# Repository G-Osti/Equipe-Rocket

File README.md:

Pasta da documentação recuperada de 2022/2023 das atividades desenvolvidas na Equipe Rocket.
Não está nem um pouco organizado.

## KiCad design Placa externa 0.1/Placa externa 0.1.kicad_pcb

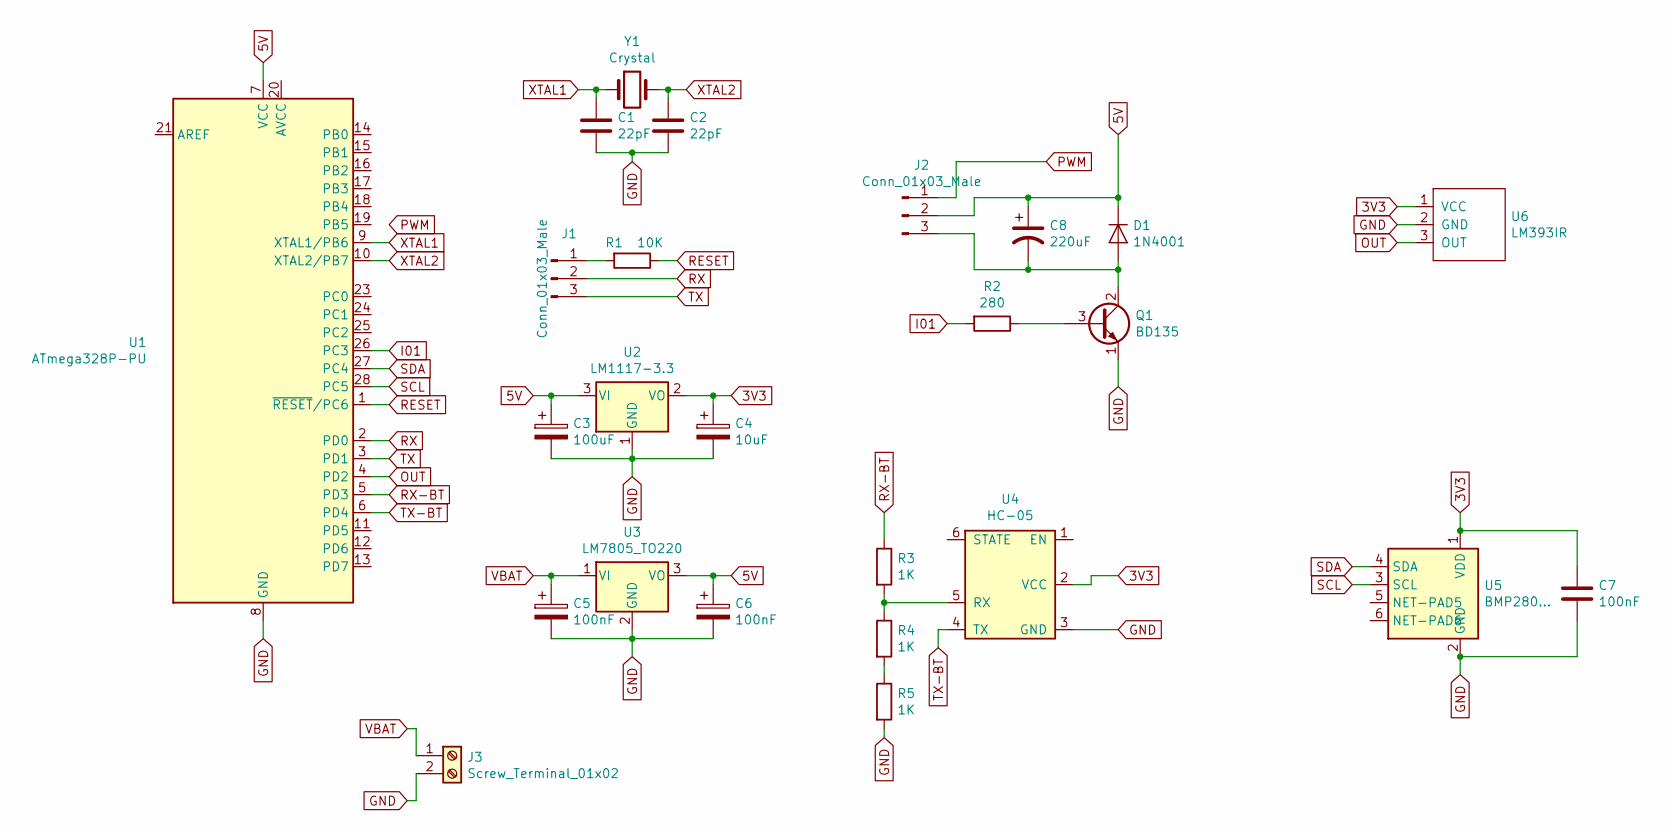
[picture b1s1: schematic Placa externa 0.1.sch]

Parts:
C1, C2: 22pF; CP_EIA-1608-08_AVX-J_Pad1.25x1.05mm_HandSolder
C3: 100uF; CP_EIA-1608-08_AVX-J_Pad1.25x1.05mm_HandSolder
C4: 10uF; CP_EIA-1608-08_AVX-J_Pad1.25x1.05mm_HandSolder
C5, C6, C7: 100nF; CP_EIA-6032-15_Kemet-U_Pad2.25x2.35mm_HandSolder
C8: 220uF; CP_EIA-1608-08_AVX-J_Pad1.25x1.05mm_HandSolder
D1: 1N4001; D_0603_1608Metric_Pad1.05x0.95mm_HandSolder
J1, J2: Conn_01x03_Male; FanPinHeader_1x03_P2.54mm_Vertical
J3: Screw_Terminal_01x02; TerminalBlock_Altech_AK300-2_P5.00mm
Q1: BD135; TO-126-3_Vertical
R1: 10K; R_0603_1608Metric_Pad1.05x0.95mm_HandSolder
R2: 280; R_0603_1608Metric_Pad1.05x0.95mm_HandSolder
R3, R4, R5: 1K; R_0603_1608Metric_Pad1.05x0.95mm_HandSolder
U1: ATmega328P-PU; DIP-28_W7.62mm
U2: LM1117-3.3; TO-3P-3_Vertical
U3: LM7805_TO220; TO-220-3_Vertical
U4: HC-05; SOIC-8_3.9x4.9mm_P1.27mm
U5: BMP280...; Bosch_LGA-8_2x2.5mm_P0.65mm_ClockwisePinNumbering
U6: LM393IR; TO-3P-3_Vertical
Y1: Crystal; Crystal_C26-LF_D2.1mm_L6.5mm_Horizontal

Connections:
3V3: C4.1, C7.1, U2.2 (VO), U4.2 (VCC), U5.1 (VDD), U6.1 (VCC)
5V: C3.1, C6.1, C8.1, D1.1 (K), J2.2, U1.7 (VCC), U2.3 (VI), U3.3 (VO)
GND: C1.2, C2.2, C3.2, C4.2, C5.2, C6.2, C7.2, J3.2, Q1.1 (E), R5.2, U1.8 (GND), U1.22 (GND), U2.1 (GND), U3.2 (GND), U4.3 (GND), U5.2 (GND), U6.2 (GND)
I01: R2.2, U1.26 (PC3)
unnamed: C8.2, D1.2 (A), J2.3, Q1.2 (C)
unnamed: J1.1, R1.2
unnamed: Q1.3 (B), R2.1
unnamed: R3.2, R4.1, U4.5 (RX)
unnamed: R4.2, R5.1
OUT: U1.4 (PD2), U6.3 (OUT)
PWM: J2.1
RESET: R1.1, U1.1 (~RESET~/PC6)
RX: J1.2, U1.2 (PD0)
RX-BT: R3.1, U1.5 (PD3)
SCL: U1.28 (PC5), U5.3 (SCL)
SDA: U1.27 (PC4), U5.4 (SDA)
TX: J1.3, U1.3 (PD1)
TX-BT: U1.6 (PD4), U4.4 (TX)
VBAT: C5.1, J3.1, U3.1 (VI)
XTAL1: C1.1, U1.9 (XTAL1/PB6), Y1.1
XTAL2: C2.1, U1.10 (XTAL2/PB7), Y1.2

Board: 2 copper layers, 25 parts (0 on the bottom side), 20 nets, no tracks yet.
